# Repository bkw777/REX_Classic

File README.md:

# REX Classic, BKW re-spin

### Directions
http://tandy.wiki/REX

Gerbers & cpld bitstream in [releases](../../releases/latest).

BOM: [DigiKey](https://www.digikey.com/short/zwwvvr2j)  
PCB & Carrier: [PCBWAY](https://www.pcbway.com/project/shareproject/REX_Classic__BKW_re_spin.html)

Ordering tips for the pcb & carrier:  
* on PCBWAY manually change the min tracks/spaces to 6mil/6mil
* For gold contacts, select ENIG copper finish
* For the carrier select material Nylon, process SLS
* PCBWAY is more expensive, especially for ENIG, and they don't have the best print option for the carrier.
  Elecrow is cheaper for ENIG, and their "High Strength Nylon" option for 3d printing is actually black nylon printed by MJF, which is the nicest for this.
  It's just that on Elecrow you have to upload the gerber zip and carrier stl from [releases](../../releases/latest), there is no pre-configured buy page.

Carrier cad source: https://github.com/bkw777/Molex78802_Module (PCB_28 variant)

### Original REX design is by Steven Adolph
http://bitchin100.com/wiki/index.php?title=REX  
http://www.club100.org/memfiles/index.php?direction=0&order=&directory=Steve%20Adolph

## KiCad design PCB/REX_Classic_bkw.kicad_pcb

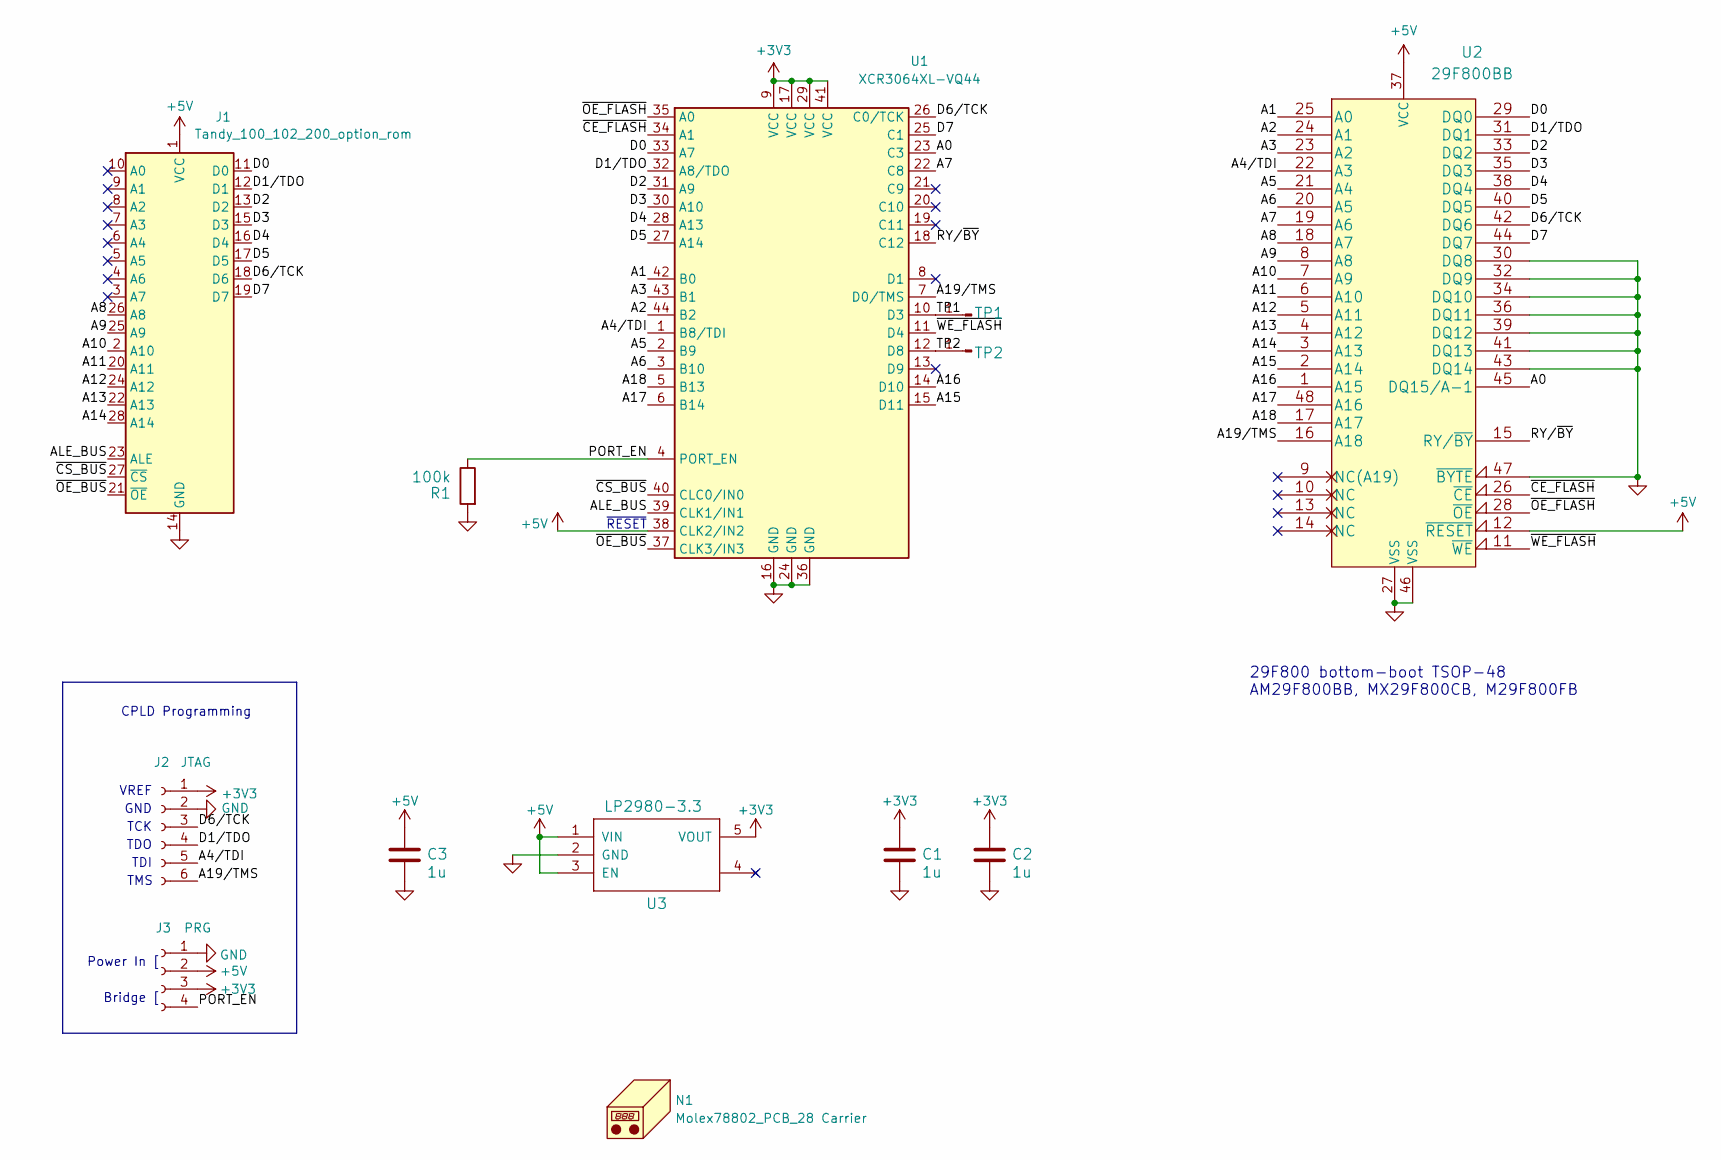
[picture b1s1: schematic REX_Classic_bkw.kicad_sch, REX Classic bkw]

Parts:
C1, C2, C3: 1u; C_0805
J1: Tandy_100_102_200_option_rom; Molex78802_PCB_28_REX
J2: JTAG; 1x6_pcb_socket
J3: PRG; 1x4_pcb_socket
N1: Molex78802_PCB_28 Carrier; Housing_Molex78802_PCB_28
R1: 100k; R_0805
TP1, TP2: PINHD-1X1; 1x1_pin_h
U1: XCR3064XL-VQ44; VQFP44; MPN XCR3064XL-VQ44
U2: 29F800BB; TSOP-48; MPN AM29F800BB
U3: LP2980-3.3; SOT-23-5; MPN LP2980-3.3

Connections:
+3V3: C1.1, C2.1, J2.1, J3.3, U1.9 (VCC), U1.17 (VCC), U1.29 (VCC), U1.41 (VCC), U3.5 (VOUT)
+5V: C3.1, J1.1 (VCC), J3.2, U1.38 (CLK2/IN2), U2.12 (~RESET), U2.37 (VCC), U3.1 (VIN), U3.3 (EN)
/A0: U1.23 (C3), U2.45 (DQ15/A-1)
/A1: U1.42 (B0), U2.25 (A0)
/A2: U1.44 (B2), U2.24 (A1)
/A3: U1.43 (B1), U2.23 (A2)
/A4/TDI: J2.5, U1.1 (B8/TDI), U2.22 (A3)
/A5: U1.2 (B9), U2.21 (A4)
/A6: U1.3 (B10), U2.20 (A5)
/A7: U1.22 (C8), U2.19 (A6)
/A8: J1.26 (A8), U2.18 (A7)
/A9: J1.25 (A9), U2.8 (A8)
/A10: J1.2 (A10), U2.7 (A9)
/A11: J1.20 (A11), U2.6 (A10)
/A12: J1.24 (A12), U2.5 (A11)
/A13: J1.22 (A13), U2.4 (A12)
/A14: J1.28 (A14), U2.3 (A13)
/A15: U1.15 (D11), U2.2 (A14)
/A16: U1.14 (D10), U2.1 (A15)
/A17: U1.6 (B14), U2.48 (A16)
/A18: U1.5 (B13), U2.17 (A17)
/A19/TMS: J2.6, U1.7 (D0/TMS), U2.16 (A18)
/ALE_BUS: J1.23 (ALE), U1.39 (CLK1/IN1)
/D0: J1.11 (D0), U1.33 (A7), U2.29 (DQ0)
/D1/TDO: J1.12 (D1), J2.4, U1.32 (A8/TDO), U2.31 (DQ1)
/D2: J1.13 (D2), U1.31 (A9), U2.33 (DQ2)
/D3: J1.15 (D3), U1.30 (A10), U2.35 (DQ3)
/D4: J1.16 (D4), U1.28 (A13), U2.38 (DQ4)
/D5: J1.17 (D5), U1.27 (A14), U2.40 (DQ5)
/D6/TCK: J1.18 (D6), J2.3, U1.26 (C0/TCK), U2.42 (DQ6)
/D7: J1.19 (D7), U1.25 (C1), U2.44 (DQ7)
/PORT_EN: J3.4, R1.1, U1.4 (PORT_EN)
/RY/~BY: U1.18 (C12), U2.15 (RY/~BY)
/TP1: TP1.1, U1.10 (D3)
/TP2: TP2.1, U1.12 (D8)
/~CE_FLASH: U1.34 (A1), U2.26 (~CE)
/~CS_BUS: J1.27 (~CS), U1.40 (CLC0/IN0)
/~OE_BUS: J1.21 (~OE), U1.37 (CLK3/IN3)
/~OE_FLASH: U1.35 (A0), U2.28 (~OE)
/~WE_FLASH: U1.11 (D4), U2.11 (~WE)
GND: C1.2, C2.2, C3.2, J1.14 (GND), J2.2, J3.1, R1.2, U1.16 (GND), U1.24 (GND), U1.36 (GND), U2.27 (VSS), U2.30 (DQ8), U2.32 (DQ9), U2.34 (DQ10), U2.36 (DQ11), U2.39 (DQ12), U2.41 (DQ13), U2.43 (DQ14), U2.46 (VSS), U2.47 (~BYTE), U3.2 (GND)

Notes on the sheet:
29F800 bottom-boot TSOP-48 AM29F800BB, MX29F800CB, M29F800FB
Power In [
TDI
TMS
CPLD Programming
GND
VREF
TCK
TDO
Bridge [
~{RESET}

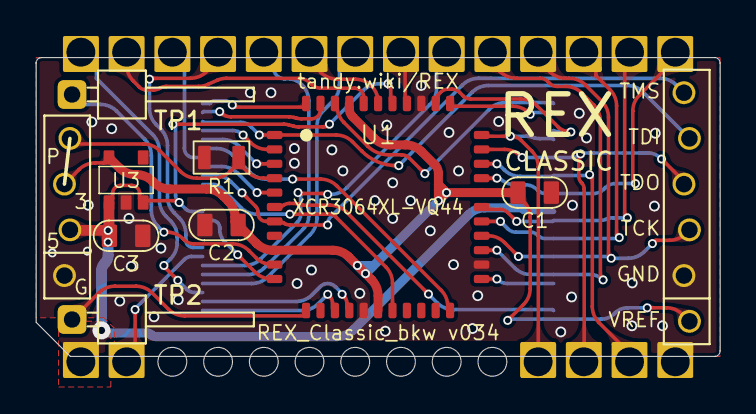
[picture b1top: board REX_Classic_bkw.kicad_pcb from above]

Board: 2 copper layers, 38.0 x 16.6 mm, 13 parts (1 on the bottom side), 41 nets.

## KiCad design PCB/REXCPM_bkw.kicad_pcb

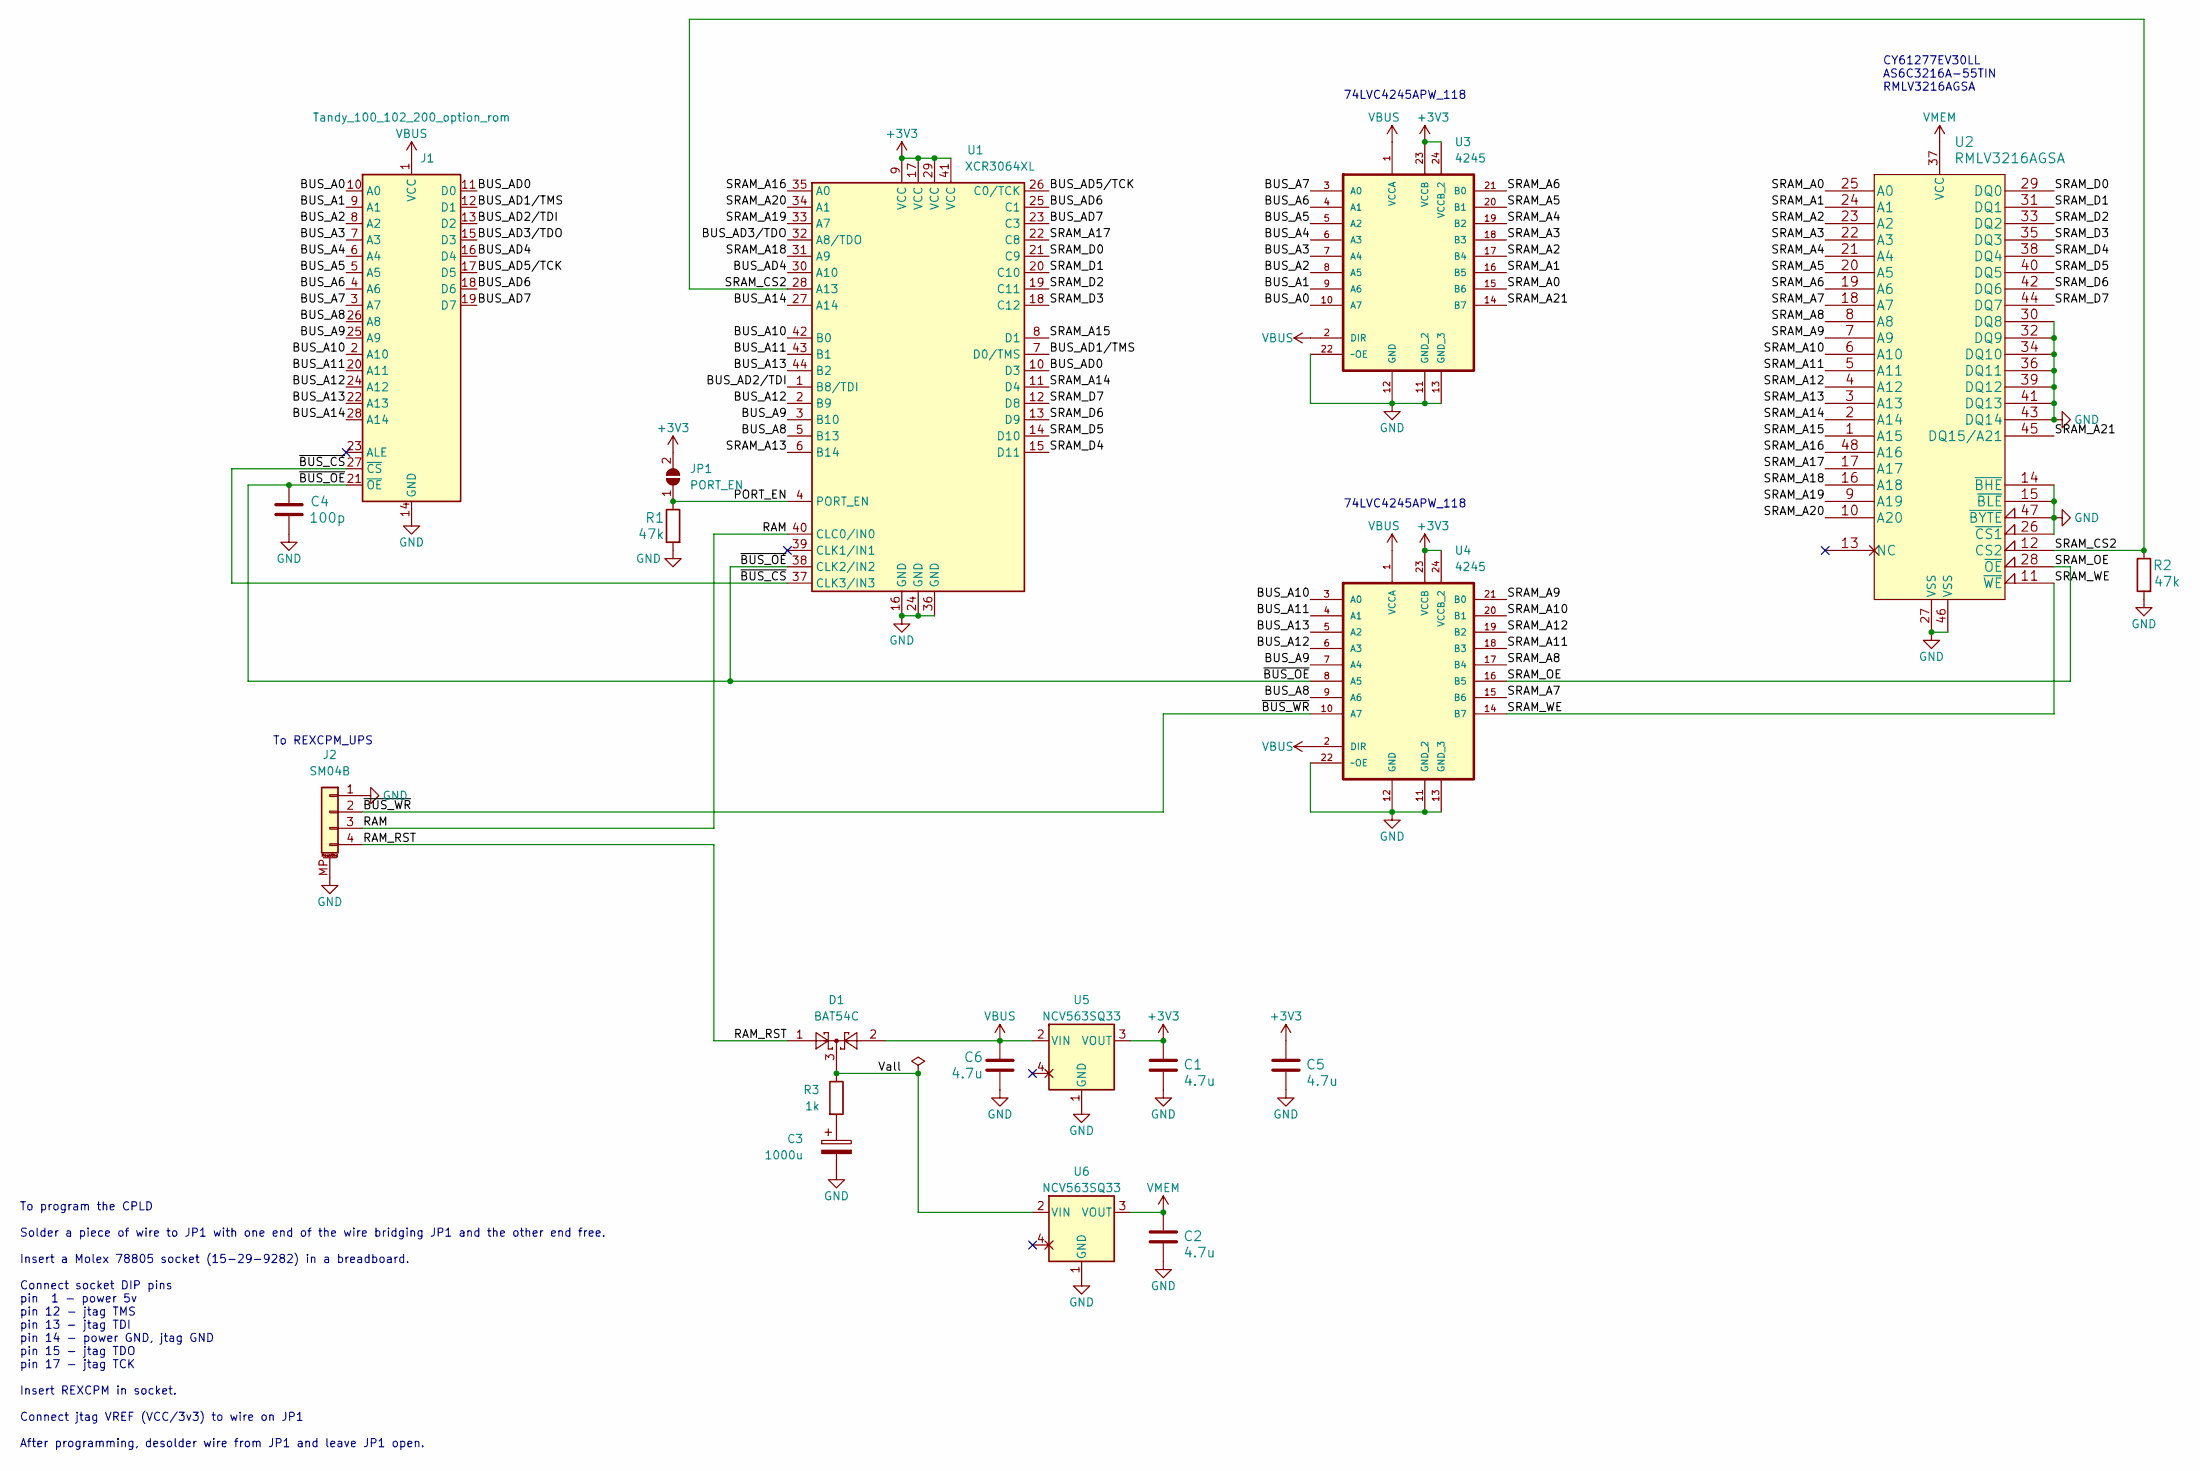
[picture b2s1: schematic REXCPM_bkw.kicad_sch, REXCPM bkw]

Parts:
C1, C2, C5, C6: 4.7u; C_0805
C3: 1000u; CP_7343-43
C4: 100p; C_0805
D1: BAT54C; SOT-23
J1: Tandy_100_102_200_option_rom; Molex78802_PCB_28_slots
J2: SM04B; JST_SH_SM04B-SRSS-TB_1x04-1MP_P1.00mm_Horizontal
JP1: PORT_EN; SolderJumper_1mm_2p_open
R1, R2: 47k; R_0805
R3: 1k; R_0805
U1: XCR3064XL; VQFP44
U2: RMLV3216AGSA; TSOP-48
U3, U4: 4245; TSSOP-24_4.4x7.8mm_P0.65mm
U5, U6: NCV563SQ33; SC-82AB

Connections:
+3V3: C1.1, C5.1, JP1.2 (B), U1.9 (VCC), U1.17 (VCC), U1.29 (VCC), U1.41 (VCC), U3.23 (VCCB), U3.24 (VCCB_2), U4.23 (VCCB), U4.24 (VCCB_2), U5.3 (VOUT)
+VSW: D1.3, R3.1, U6.2 (VIN)
/BUS_A0: J1.10 (A0), U3.10 (A7)
/BUS_A1: J1.9 (A1), U3.9 (A6)
/BUS_A2: J1.8 (A2), U3.8 (A5)
/BUS_A3: J1.7 (A3), U3.7 (A4)
/BUS_A4: J1.6 (A4), U3.6 (A3)
/BUS_A5: J1.5 (A5), U3.5 (A2)
/BUS_A6: J1.4 (A6), U3.4 (A1)
/BUS_A7: J1.3 (A7), U3.3 (A0)
/BUS_A8: J1.26 (A8), U1.5 (B13), U4.9 (A6)
/BUS_A9: J1.25 (A9), U1.3 (B10), U4.7 (A4)
/BUS_A10: J1.2 (A10), U1.42 (B0), U4.3 (A0)
/BUS_A11: J1.20 (A11), U1.43 (B1), U4.4 (A1)
/BUS_A12: J1.24 (A12), U1.2 (B9), U4.6 (A3)
/BUS_A13: J1.22 (A13), U1.44 (B2), U4.5 (A2)
/BUS_A14: J1.28 (A14), U1.27 (A14)
/BUS_AD0: J1.11 (D0), U1.10 (D3)
/BUS_AD1/TMS: J1.12 (D1), U1.7 (D0/TMS)
/BUS_AD2/TDI: J1.13 (D2), U1.1 (B8/TDI)
/BUS_AD3/TDO: J1.15 (D3), U1.32 (A8/TDO)
/BUS_AD4: J1.16 (D4), U1.30 (A10)
/BUS_AD5/TCK: J1.17 (D5), U1.26 (C0/TCK)
/BUS_AD6: J1.18 (D6), U1.25 (C1)
/BUS_AD7: J1.19 (D7), U1.23 (C3)
/PORT_EN: JP1.1 (A), R1.1, U1.4 (PORT_EN)
/RAM: J2.3, U1.40 (CLC0/IN0)
/RAM_RST: D1.1, J2.4
/SRAM_A0: U2.25 (A0), U3.15 (B6)
/SRAM_A1: U2.24 (A1), U3.16 (B5)
/SRAM_A2: U2.23 (A2), U3.17 (B4)
/SRAM_A3: U2.22 (A3), U3.18 (B3)
/SRAM_A4: U2.21 (A4), U3.19 (B2)
/SRAM_A5: U2.20 (A5), U3.20 (B1)
/SRAM_A6: U2.19 (A6), U3.21 (B0)
/SRAM_A7: U2.18 (A7), U4.15 (B6)
/SRAM_A8: U2.8 (A8), U4.17 (B4)
/SRAM_A9: U2.7 (A9), U4.21 (B0)
/SRAM_A10: U2.6 (A10), U4.20 (B1)
/SRAM_A11: U2.5 (A11), U4.18 (B3)
/SRAM_A12: U2.4 (A12), U4.19 (B2)
/SRAM_A13: U1.6 (B14), U2.3 (A13)
/SRAM_A14: U1.11 (D4), U2.2 (A14)
/SRAM_A15: U1.8 (D1), U2.1 (A15)
/SRAM_A16: U1.35 (A0), U2.48 (A16)
/SRAM_A17: U1.22 (C8), U2.17 (A17)
/SRAM_A18: U1.31 (A9), U2.16 (A18)
/SRAM_A19: U1.33 (A7), U2.9 (A19)
/SRAM_A20: U1.34 (A1), U2.10 (A20)
/SRAM_A21: U2.45 (DQ15/A21), U3.14 (B7)
/SRAM_CS2: R2.1, U1.28 (A13), U2.12 (CS2)
/SRAM_D0: U1.21 (C9), U2.29 (DQ0)
/SRAM_D1: U1.20 (C10), U2.31 (DQ1)
/SRAM_D2: U1.19 (C11), U2.33 (DQ2)
/SRAM_D3: U1.18 (C12), U2.35 (DQ3)
/SRAM_D4: U1.15 (D11), U2.38 (DQ4)
/SRAM_D5: U1.14 (D10), U2.40 (DQ5)
/SRAM_D6: U1.13 (D9), U2.42 (DQ6)
/SRAM_D7: U1.12 (D8), U2.44 (DQ7)
/SRAM_OE: U2.28 (~OE), U4.16 (B5)
/SRAM_WE: U2.11 (~WE), U4.14 (B7)
/~BUS_CS: J1.27 (~CS), U1.37 (CLK3/IN3)
/~BUS_OE: C4.1, J1.21 (~OE), U1.38 (CLK2/IN2), U4.8 (A5)
/~BUS_WR: J2.2, U4.10 (A7)
GND: C1.2, C2.2, C3.2, C4.2, C5.2, C6.2, J1.14 (GND), J2.1, J2.MP (MountPin), R1.2, R2.2, U1.16 (GND), U1.24 (GND), U1.36 (GND), U2.14 (~BHE), U2.15 (~BLE), U2.26 (~CS1), U2.27 (VSS), U2.30 (DQ8), U2.32 (DQ9), U2.34 (DQ10), U2.36 (DQ11), U2.39 (DQ12), U2.41 (DQ13), U2.43 (DQ14), U2.46 (VSS), U2.47 (~BYTE), U3.11 (GND_2), U3.12 (GND), U3.13 (GND_3), U3.22 (~OE), U4.11 (GND_2), U4.12 (GND), U4.13 (GND_3), U4.22 (~OE), U5.1 (GND), U6.1 (GND)
unnamed: C3.1, R3.2
VBUS: C6.1, D1.2, J1.1 (VCC), U3.1 (VCCA), U3.2 (DIR), U4.1 (VCCA), U4.2 (DIR), U5.2 (VIN)
VMEM: C2.1, U2.37 (VCC), U6.3 (VOUT)

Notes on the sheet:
To program the CPLD Solder a piece of wire to JP1 with one end of the wire bridging JP1 and the other end free. Insert a Molex 78805 socket (15-29-9282) in a breadboard. Connect socket DIP pins pin 1 - power 5v pin 12 - jtag TMS pin 13 - jtag TDI pin 14 - power GND, jtag GND pin 15 - jtag TDO pin 1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
74LVC4245APW_118
To REXCPM_UPS
CY61277EV30LL AS6C3216A-55TIN RMLV3216AGSA

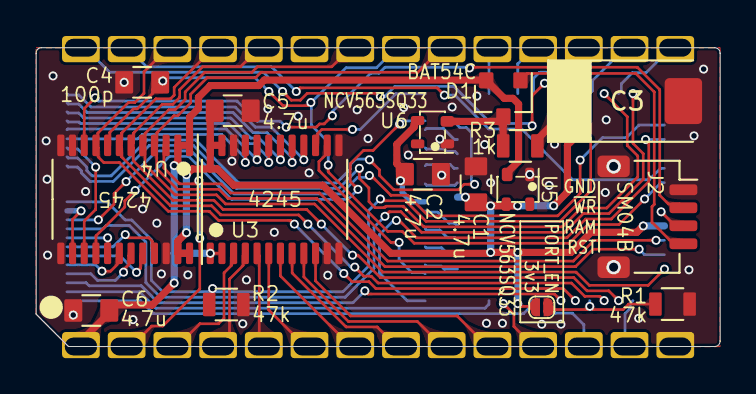
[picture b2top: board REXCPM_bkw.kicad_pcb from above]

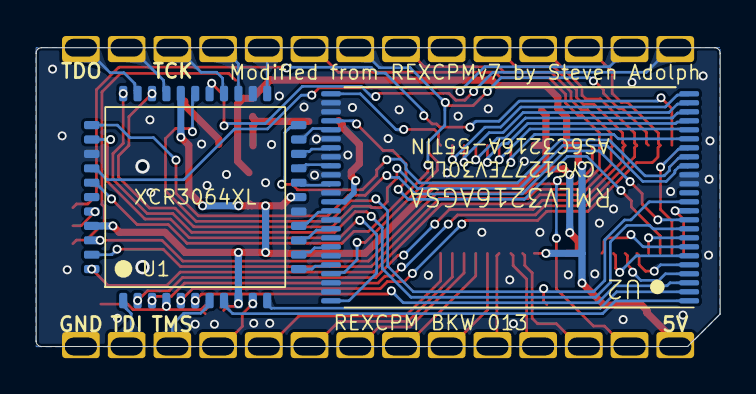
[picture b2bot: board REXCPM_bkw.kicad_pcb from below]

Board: 2 copper layers, 38.0 x 16.6 mm, 19 parts (2 on the bottom side), 68 nets.

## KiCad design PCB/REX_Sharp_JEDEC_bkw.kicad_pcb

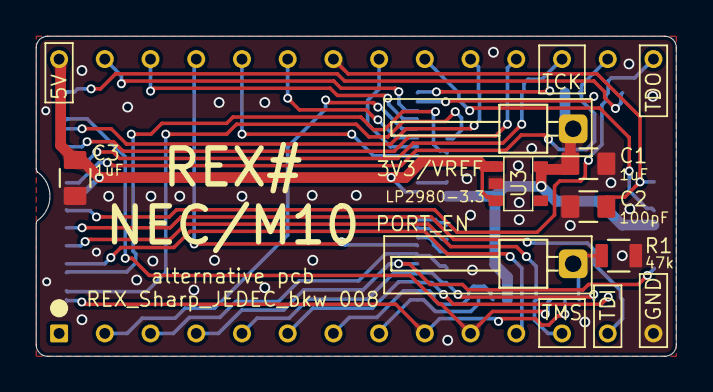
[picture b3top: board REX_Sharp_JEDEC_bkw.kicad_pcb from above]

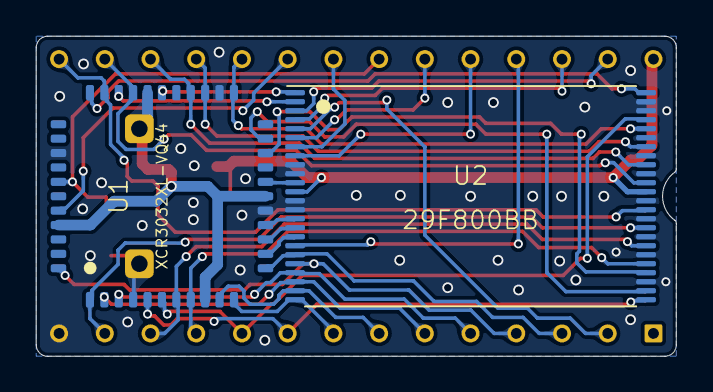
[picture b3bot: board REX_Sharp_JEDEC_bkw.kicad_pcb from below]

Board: 2 copper layers, 35.6 x 17.8 mm, 10 parts (2 on the bottom side), 38 nets.

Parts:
C1, C3: 1uF; C_0805
C2: 100pF; C_0805
J1: Option-ROM SOCKET; DIP-28_600_pcb_shallow_notch
R1: 47k; R_0805
TP1: PORT_EN; 1x1_pin_h
TP2: 3V3/VREF; 1x1_pin_h
U1: XCR3032XL-VQ44; VQFP44
U2: 29F800BB; TSOP-48
U3: LP2980-3.3; SOT-23-5

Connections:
+3V3: C1.1, TP2.1, U1.9 (VCC), U1.17 (VCC), U1.29 (VCC), U1.41 (VCC), U3.5 (VOUT)
+5V: C3.1, J1.28 (VCC), U2.12 (~RESET), U2.37 (VCC), U3.1 (VIN), U3.3 (EN)
/A0: J1.10 (A0), U1.6 (B14), U2.45 (DQ15/A-1)
/A1: J1.9 (A1), U1.5 (B13), U2.25 (A0)
/A2: J1.8 (A2), U1.11 (D4), U2.24 (A1)
/A3: J1.7 (A3), U1.10 (D3), U2.23 (A2)
/A4: J1.6 (A4), U1.2 (B9), U2.22 (A3)
/A5: J1.5 (A5), U1.3 (B10), U2.21 (A4)
/A6: J1.4 (A6), U1.44 (B2), U2.20 (A5)
/A7: J1.3 (A7), U1.12 (D8), U2.19 (A6)
/A8: J1.25 (A8), U2.18 (A7)
/A9: J1.24 (A9), U2.8 (A8)
/A10: J1.21 (A10), U2.7 (A9)
/A11: J1.23 (A11), U2.6 (A10)
/A12: J1.2 (A12), U2.5 (A11)
/A13: J1.26 (A13), U2.4 (A12)
/A14: J1.27 (A14), U2.3 (A13)
/A15: U1.31 (A9), U2.2 (A14)
/A16: U1.28 (A13), U2.1 (A15)
/A17: U1.33 (A7), U2.48 (A16)
/A18: U1.13 (D9), U2.17 (A17)
/A19: U1.14 (D10), U2.16 (A18)
/D0: J1.11 (D0), U1.8 (D1), U2.29 (DQ0)
/D1/TMS: J1.12 (D1), U1.7 (D0/TMS), U2.31 (DQ1)
/D2/TDI: J1.13 (D2), U1.1 (B8/TDI), U2.33 (DQ2)
/D3/TDO: J1.15 (D3), U1.32 (A8/TDO), U2.35 (DQ3)
/D4: J1.16 (D4), U1.30 (A10), U2.38 (DQ4)
/D5/TCK: J1.17 (D5), U1.26 (C0/TCK), U2.40 (DQ5)
/D6: J1.18 (D6), U1.25 (C1), U2.42 (DQ6)
/D7: J1.19 (D7), U1.23 (C3), U2.44 (DQ7)
/PORT_EN: R1.2, TP1.1, U1.4 (PORT_EN)
/RY/~BY: U1.15 (D11), U2.15 (RY/~BY)
/~BUS_CS: J1.20 (~CE), U1.40 (CLC0/IN0)
/~BUS_OE: C2.1, J1.22 (~OE), U1.38 (CLK2/IN2)
/~SRAM_CE: U1.21 (C9), U2.26 (~CE)
/~SRAM_OE: U1.20 (C10), U2.28 (~OE)
/~SRAM_WE: U1.18 (C12), U2.11 (~WE)
GND: C1.2, C2.2, C3.2, J1.14 (GND), R1.1, U1.16 (GND), U1.24 (GND), U1.36 (GND), U2.9 (NC(A19)), U2.10 (NC), U2.13 (NC), U2.14 (NC), U2.27 (VSS), U2.30 (DQ8), U2.32 (DQ9), U2.34 (DQ10), U2.36 (DQ11), U2.39 (DQ12), U2.41 (DQ13), U2.43 (DQ14), U2.46 (VSS), U2.47 (~BYTE), U3.2 (GND)

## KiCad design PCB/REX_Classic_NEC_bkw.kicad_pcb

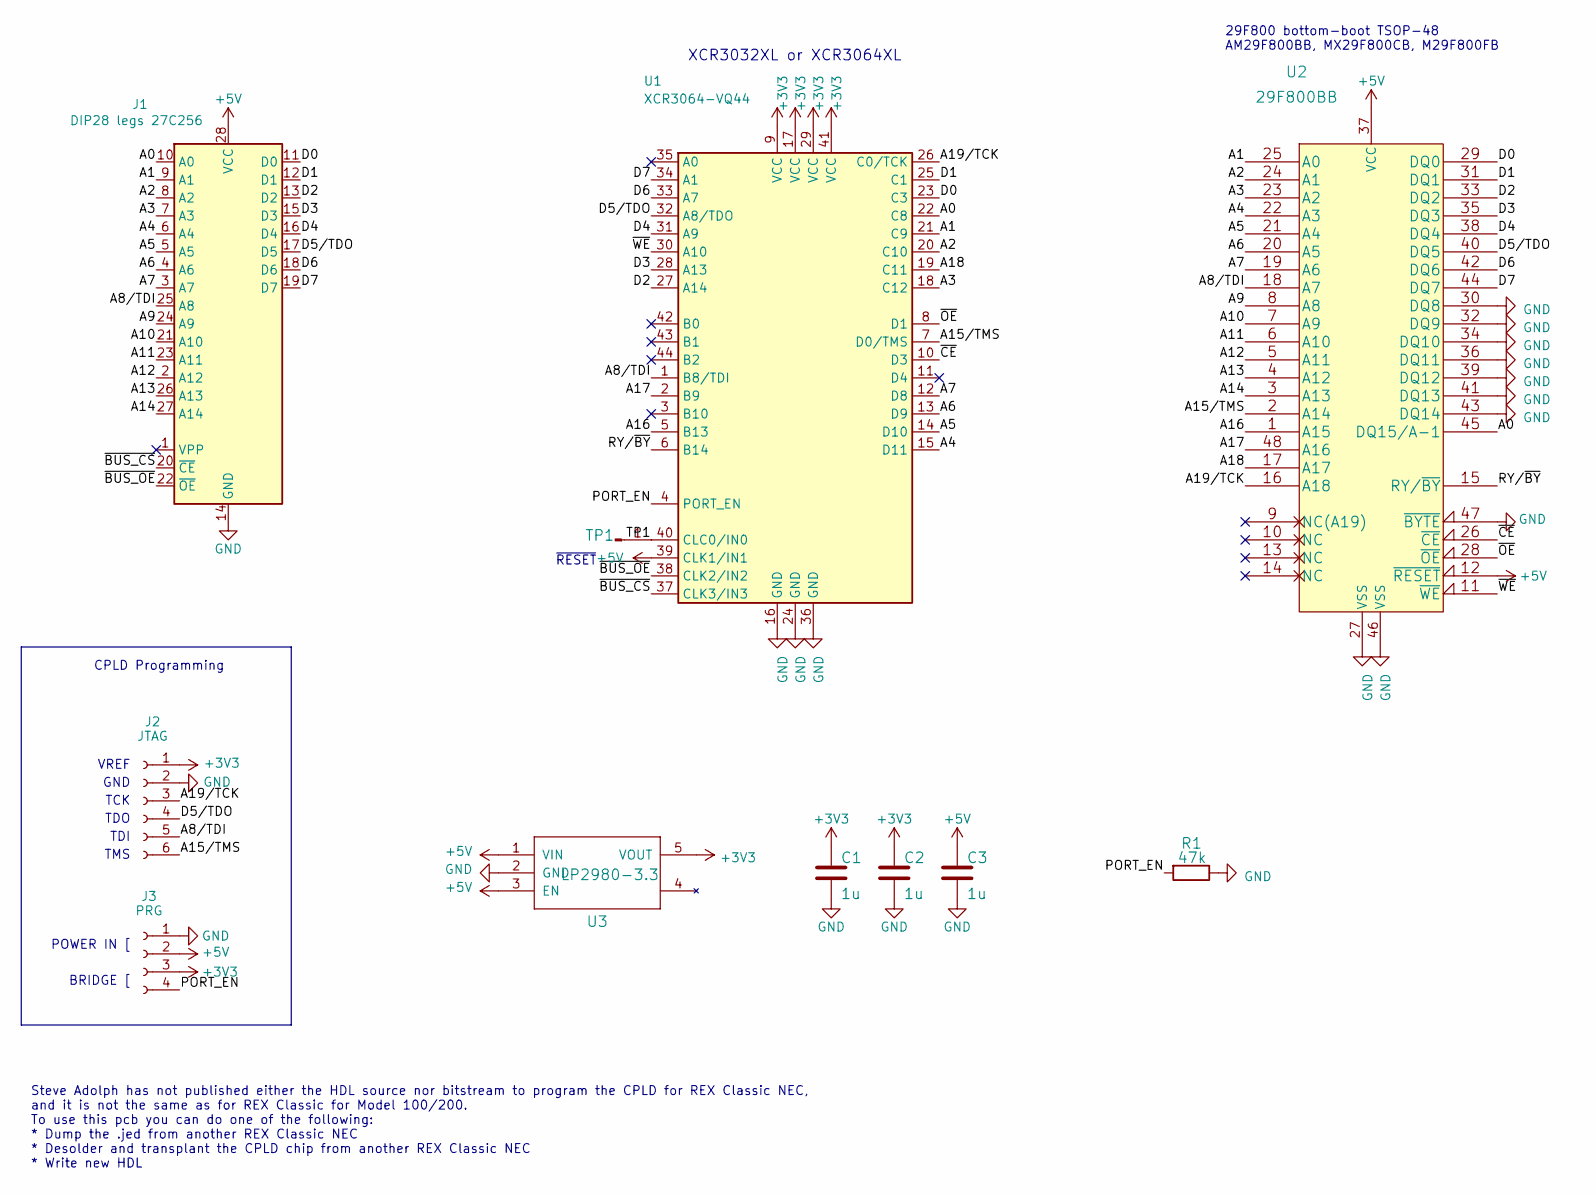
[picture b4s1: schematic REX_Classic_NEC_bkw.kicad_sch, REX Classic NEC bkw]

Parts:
C1, C2, C3: 1u; C_0805
J1: DIP28 legs 27C256; DIP-28_600_pcb_shallow_notch
J2: JTAG; 1x6_pcb_socket
J3: PRG; 1x4_pcb_socket
R1: 47k; R_0805
TP1: PINHD-1X1; 1x1_pin_h
U1: XCR3064-VQ44; VQFP44
U2: 29F800BB; TSOP-48
U3: LP2980-3.3; SOT-23-5

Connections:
+3V3: C1.1, C2.1, J2.1, J3.3, U1.9 (VCC), U1.17 (VCC), U1.29 (VCC), U1.41 (VCC), U3.5 (VOUT)
+5V: C3.1, J1.28 (VCC), J3.2, U1.39 (CLK1/IN1), U2.12 (~RESET), U2.37 (VCC), U3.1 (VIN), U3.3 (EN)
/A0: J1.10 (A0), U1.22 (C8), U2.45 (DQ15/A-1)
/A1: J1.9 (A1), U1.21 (C9), U2.25 (A0)
/A2: J1.8 (A2), U1.20 (C10), U2.24 (A1)
/A3: J1.7 (A3), U1.18 (C12), U2.23 (A2)
/A4: J1.6 (A4), U1.15 (D11), U2.22 (A3)
/A5: J1.5 (A5), U1.14 (D10), U2.21 (A4)
/A6: J1.4 (A6), U1.13 (D9), U2.20 (A5)
/A7: J1.3 (A7), U1.12 (D8), U2.19 (A6)
/A8/TDI: J1.25 (A8), J2.5, U1.1 (B8/TDI), U2.18 (A7)
/A9: J1.24 (A9), U2.8 (A8)
/A10: J1.21 (A10), U2.7 (A9)
/A11: J1.23 (A11), U2.6 (A10)
/A12: J1.2 (A12), U2.5 (A11)
/A13: J1.26 (A13), U2.4 (A12)
/A14: J1.27 (A14), U2.3 (A13)
/A15/TMS: J2.6, U1.7 (D0/TMS), U2.2 (A14)
/A16: U1.5 (B13), U2.1 (A15)
/A17: U1.2 (B9), U2.48 (A16)
/A18: U1.19 (C11), U2.17 (A17)
/A19/TCK: J2.3, U1.26 (C0/TCK), U2.16 (A18)
/D0: J1.11 (D0), U1.23 (C3), U2.29 (DQ0)
/D1: J1.12 (D1), U1.25 (C1), U2.31 (DQ1)
/D2: J1.13 (D2), U1.27 (A14), U2.33 (DQ2)
/D3: J1.15 (D3), U1.28 (A13), U2.35 (DQ3)
/D4: J1.16 (D4), U1.31 (A9), U2.38 (DQ4)
/D5/TDO: J1.17 (D5), J2.4, U1.32 (A8/TDO), U2.40 (DQ5)
/D6: J1.18 (D6), U1.33 (A7), U2.42 (DQ6)
/D7: J1.19 (D7), U1.34 (A1), U2.44 (DQ7)
/PORT_EN: J3.4, R1.2, U1.4 (PORT_EN)
/RY/~BY: U1.6 (B14), U2.15 (RY/~BY)
/TP1: TP1.1, U1.40 (CLC0/IN0)
/~BUS_CS: J1.20 (~CE), U1.37 (CLK3/IN3)
/~BUS_OE: J1.22 (~OE), U1.38 (CLK2/IN2)
/~CE: U1.10 (D3), U2.26 (~CE)
/~OE: U1.8 (D1), U2.28 (~OE)
/~WE: U1.30 (A10), U2.11 (~WE)
GND: C1.2, C2.2, C3.2, J1.14 (GND), J2.2, J3.1, R1.1, U1.16 (GND), U1.24 (GND), U1.36 (GND), U2.27 (VSS), U2.30 (DQ8), U2.32 (DQ9), U2.34 (DQ10), U2.36 (DQ11), U2.39 (DQ12), U2.41 (DQ13), U2.43 (DQ14), U2.46 (VSS), U2.47 (~BYTE), U3.2 (GND)

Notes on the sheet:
TCK
POWER IN [
TMS
GND
~{RESET}
TDO
BRIDGE [
TDI
29F800 bottom-boot TSOP-48 AM29F800BB, MX29F800CB, M29F800FB
XCR3032XL or XCR3064XL
VREF
CPLD Programming
Steve Adolph has not published either the HDL source nor bitstream to program the CPLD for REX Classic NEC, and it is not the same as for REX Classic for Model 100/200. To use this pcb you can do one of the following: * Dump the .jed from another REX Classic NEC * Desolder and transplant the CPLD c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

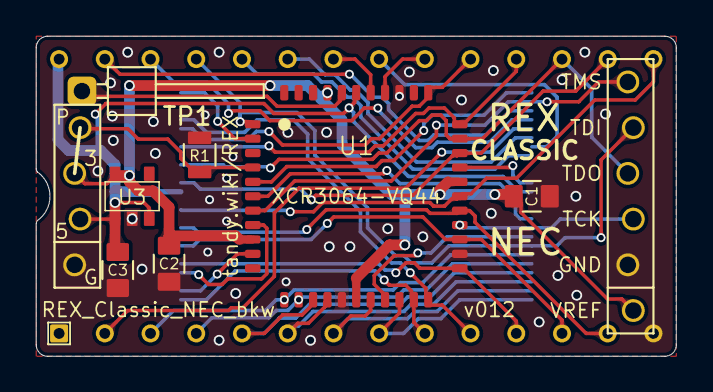
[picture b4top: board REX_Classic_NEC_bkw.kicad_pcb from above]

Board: 2 copper layers, 35.6 x 17.8 mm, 11 parts (1 on the bottom side), 39 nets.

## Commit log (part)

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2018-04-29 Original Commit Original source was Rex.brd from REX_STD.zip from Steve Adolph on Club100.org Rex.brd was an EagleCAD file, but not recognized/importable/convertable by any utils at this time. Rex.br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
2019-09-12 initial commit bkw c11 version
2020-02-05 slightly reduced outside dimensions or 3d print variability
2020-02-06 reduce X & Y for 3d printing variability
2020-02-20 nonsense trace nudging
2020-02-20 nudge
2020-02-20 initial NEC 8201a version
2020-02-20 move TP1 & TP2 pins so dupont connector fits better between cpld and socket
2020-02-21 correct silkscreen leadframe part#
2020-02-21 silkscreen
2020-02-29 update to latest pcb2molex8878 carrier and pcb outline
2020-03-24 8201 v2 using freerouting autorouter followed by manual fixups
2020-04-04 remove junk
2020-04-04 add more junk to gitignore
2020-04-04 names
2020-06-10 remove some sharp inside angles. move c1 on nec.
2020-12-01 flip ram and reroute nec board, several other minor touches both boards
2020-12-01 larger vias for cheaper manufacturing
2021-03-08 Less expensive manufacturing tolerances. Rename to REX Classic.
2021-03-15 min drill 0.3mm for PCBWAY, replace GND traces with zone fill
2021-03-17 rename pcb2molex8878 to Molex78805_PCB
2021-04-27 clearances
2021-05-23 gitignore
2021-05-23 upgrade board outline and carrier to v004
2021-05-23 readme
2021-07-05 remove pointless busses from sch, minor silkscreen tweaks
2021-07-07 clearance around some traces & vias
2021-07-08 clearances, remove pointless busses in schematic
2022-09-07 ignore new v6 and plugin files
2022-09-07 v024, 0.2mm spaces, thicker power traces
2023-07-04 kicad 7, 0.2mm tracks, 0.3x0.5mm vias, add caps on 3v3
2023-07-04 min text/line sizes in some footprints
2023-07-05 small layout nudges
2023-10-09 rexcpm
2023-10-09 streamline rexcpm routing
2023-11-06 rexcpm small layout opts
2023-11-06 rexcpm qwiic connector
2023-11-06 rexcpm add cap on vbus
2023-11-08 reorganize repo files
2024-03-06 carrier 3d model and kicad 8
2024-03-23 0805 footprints, minor trace adjustments
2024-03-23 renders
2024-03-23 plot settings
2024-07-21 vhdl: comment unused pin in ucf, xise project file for build settings, actually builds
2024-07-21 docs
2024-07-21 license
2025-01-02 add sharp-tandy
2025-02-01 remove dead shapeways url for carrier
